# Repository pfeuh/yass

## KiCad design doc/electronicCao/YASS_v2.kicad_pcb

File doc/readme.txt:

Concerning Yass, all is shared.

Box data is explaned in yassBox.txt.
Schematic is in this folder.
To make the PCB, data is in fab folder.

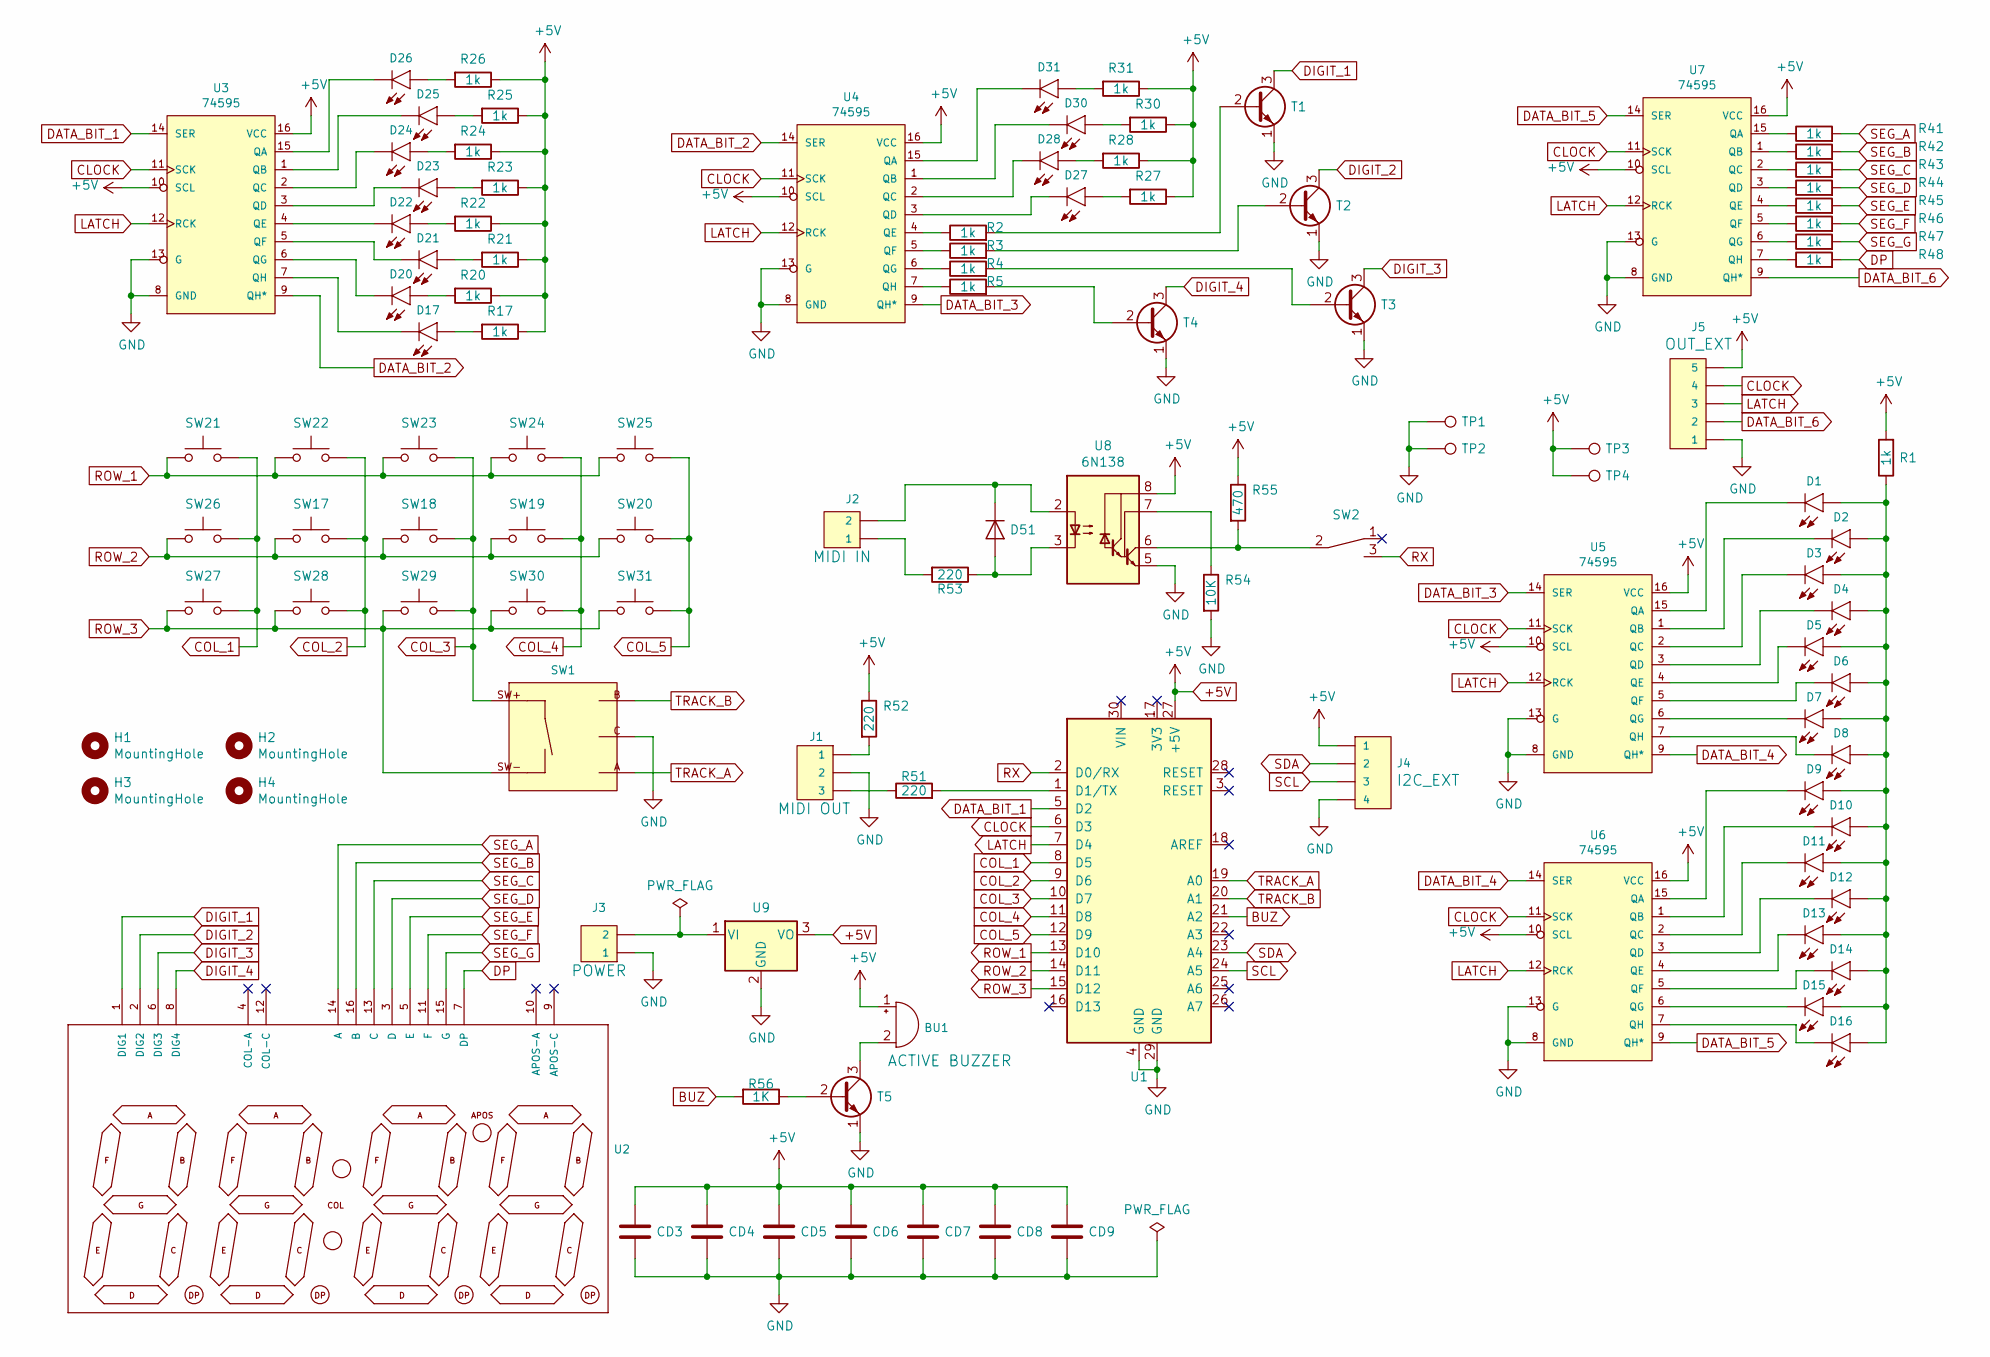
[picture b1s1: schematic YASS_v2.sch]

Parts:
BU1: BUZZER-PTH_KIT_NO_SILK; MagneticBuzzer_ProSignal_ABI-009-RC
CD3, CD4, CD5, CD6, CD7, CD8, CD9: 100nF; C_Disc_D4.3mm_W1.9mm_P5.00mm
D1, D2, D3, D4, D5, D6, D7, D8, D9, D10, D11, D12, D13, D14, D15, D16, D20: 3mm red; LED_3MM
D17: 3mm green; LED_3MM
D21, D22, D23, D24, D25: 3mm blue; LED_3MM
D26, D27, D28, D30, D31: 3mm yellow; LED_3MM
D51: 1N4148; DIODE
H1, H2, H3, H4: MountingHole; MountingHole_3.2mm_M3
J1: CONN_03; 1X03
J2: CONN_02; 1X02
J3: POWER CONNECTOR; 1X02
J4: CONN_04; 1X04
J5: CONN_05; 1X05
R1, R2, R3, R4, R5, R17, R20, R21, R22, R23, R24, R25, R26, R27, R28, R30, R31, R41, R42, R43, R44, R45, R46, R47, R48: 1k; R
R51, R52, R53: 220; R
R54: 10K; R
R55: 470; R
R56: 1K; R_Axial_DIN0207_L6.3mm_D2.5mm_P10.16mm_Horizontal
SW1: ENCODER-SWITCH; ROTARY_ENCODER
SW2: SWITCH_TOGGLE_SPST_RIGHT_ANGLE; SWITCH_SPDT_PTH_11.6X4.0MM
SW17, SW18, SW19, SW20, SW21, SW22, SW23, SW24, SW25, SW26, SW27, SW28, SW29, SW30, SW31: SW_Push; KEY_PUSH_6mm
T1, T3, T4, T5: 2N2222; TO-92_Inline_Narrow_Oval
T2: PN2222A; TO-92_Inline_Narrow_Oval
TP1, TP2, TP3, TP4: TestPoint; 1X01
U1: Arduino_Nano_v2.x; Arduino_Nano
U2: 7-SEGMENT-4DIGIT-10MM-RED; 4x7segments
U3, U4, U5, U6, U7: 74595; DIP16
U8: 6N138; DIP-8_W7.62mm
U9: LM7805_TO220; TO-220

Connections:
+5V: BU1.1 (-), CD3.1, CD4.1, CD5.1, CD6.1, CD7.1, CD8.1, CD9.1, J4.1, J5.5, R1.2, R17.1, R20.1, R21.1, R22.1, R23.1, R24.1, R25.1, R26.1, R27.1, R28.1, R30.1, R31.1, R52.1, R55.1, TP3.1, TP4.1, U1.27 (+5V), U3.10 (SCL), U3.16 (VCC), U4.10 (SCL), U4.16 (VCC), U5.10 (SCL), U5.16 (VCC), U6.10 (SCL), U6.16 (VCC), U7.10 (SCL), U7.16 (VCC), U8.8 (VCC), U9.3 (VO)
BUZ: R56.2, U1.21 (A2)
CLOCK: J5.4, U1.6 (D3), U3.11 (SCK), U4.11 (SCK), U5.11 (SCK), U6.11 (SCK), U7.11 (SCK)
COL_1: SW21.2, SW26.2, SW27.2, U1.8 (D5)
COL_2: SW17.2, SW22.2, SW28.2, U1.9 (D6)
COL_3: SW1.SW+, SW18.2, SW23.2, SW29.2, U1.10 (D7)
COL_4: SW19.2, SW24.2, SW30.2, U1.11 (D8)
COL_5: SW20.2, SW25.2, SW31.2, U1.12 (D9)
DATA_BIT_1: U1.5 (D2), U3.14 (SER)
DATA_BIT_2: U3.9 (QH*), U4.14 (SER)
DATA_BIT_3: U4.9 (QH*), U5.14 (SER)
DATA_BIT_4: U5.9 (QH*), U6.14 (SER)
DATA_BIT_5: U6.9 (QH*), U7.14 (SER)
DATA_BIT_6: J5.2, U7.9 (QH*)
DIGIT_1: T1.3 (C), U2.1 (DIG1)
DIGIT_2: T2.3 (C), U2.2 (DIG2)
DIGIT_3: T3.3 (C), U2.6 (DIG3)
DIGIT_4: T4.3 (C), U2.8 (DIG4)
DP: R48.2, U2.7 (DP)
GND: CD3.2, CD4.2, CD5.2, CD6.2, CD7.2, CD8.2, CD9.2, J1.2, J3.1, J4.4, J5.1, R54.2, SW1.C, T1.1 (E), T2.1 (E), T3.1 (E), T4.1 (E), T5.1 (E), TP1.1, TP2.1, U1.4 (GND), U1.29 (GND), U3.8 (GND), U3.13 (G), U4.8 (GND), U4.13 (G), U5.8 (GND), U5.13 (G), U6.8 (GND), U6.13 (G), U7.8 (GND), U7.13 (G), U8.5 (GND), U9.2 (GND)
LATCH: J5.3, U1.7 (D4), U3.12 (RCK), U4.12 (RCK), U5.12 (RCK), U6.12 (RCK), U7.12 (RCK)
unnamed: BU1.2 (+), T5.3 (C)
unnamed: D1.A, D2.A, D3.A, D4.A, D5.A, D6.A, D7.A, D8.A, D9.A, D10.A, D11.A, D12.A, D13.A, D14.A, D15.A, D16.A, R1.1
unnamed: D1.K (C), U5.15 (QA)
unnamed: D2.K (C), U5.1 (QB)
unnamed: D3.K (C), U5.2 (QC)
unnamed: D4.K (C), U5.3 (QD)
unnamed: D5.K (C), U5.4 (QE)
unnamed: D6.K (C), U5.5 (QF)
unnamed: D7.K (C), U5.6 (QG)
unnamed: D8.K (C), U5.7 (QH)
unnamed: D9.K (C), U6.15 (QA)
unnamed: D10.K (C), U6.1 (QB)
unnamed: D11.K (C), U6.2 (QC)
unnamed: D12.K (C), U6.3 (QD)
unnamed: D13.K (C), U6.4 (QE)
unnamed: D14.K (C), U6.5 (QF)
unnamed: D15.K (C), U6.6 (QG)
unnamed: D16.K (C), U6.7 (QH)
unnamed: D17.A, R17.2
unnamed: D17.K (C), U3.7 (QH)
unnamed: D20.A, R20.2
unnamed: D20.K (C), U3.6 (QG)
unnamed: D21.A, R21.2
unnamed: D21.K (C), U3.5 (QF)
unnamed: D22.A, R22.2
unnamed: D22.K (C), U3.4 (QE)
unnamed: D23.A, R23.2
unnamed: D23.K (C), U3.3 (QD)
unnamed: D24.A, R24.2
unnamed: D24.K (C), U3.2 (QC)
unnamed: D25.A, R25.2
unnamed: D25.K (C), U3.1 (QB)
unnamed: D26.A, R26.2
unnamed: D26.K (C), U3.15 (QA)
unnamed: D27.A, R27.2
unnamed: D27.K (C), U4.3 (QD)
unnamed: D28.A, R28.2
unnamed: D28.K (C), U4.2 (QC)
unnamed: D30.A, R30.2
unnamed: D30.K (C), U4.1 (QB)
unnamed: D31.A, R31.2
unnamed: D31.K (C), U4.15 (QA)
unnamed: D51.1 (K), J2.2, U8.2 (C1)
unnamed: D51.2 (A), R53.1, U8.3 (C2)
unnamed: J1.1, R52.2
unnamed: J1.3, R51.1
unnamed: J2.1, R53.2
unnamed: J3.2, U9.1 (VI)
unnamed: R2.1, U4.4 (QE)
unnamed: R2.2, T1.2 (B)
unnamed: R3.1, U4.5 (QF)
unnamed: R3.2, T2.2 (B)
unnamed: R4.1, U4.6 (QG)
unnamed: R4.2, T3.2 (B)
unnamed: R5.1, U4.7 (QH)
unnamed: R5.2, T4.2 (B)
unnamed: R41.1, U7.15 (QA)
unnamed: R42.1, U7.1 (QB)
unnamed: R43.1, U7.2 (QC)
unnamed: R44.1, U7.3 (QD)
unnamed: R45.1, U7.4 (QE)
unnamed: R46.1, U7.5 (QF)
unnamed: R47.1, U7.6 (QG)
unnamed: R48.1, U7.7 (QH)
unnamed: R51.2, U1.1 (D1/TX)
unnamed: R54.1, U8.7 (VO1)
unnamed: R55.2, SW2.2, U8.6 (VO2)
unnamed: R56.1, T5.2 (B)
ROW_1: SW21.1, SW22.1, SW23.1, SW24.1, SW25.1, U1.13 (D10)
ROW_2: SW17.1, SW18.1, SW19.1, SW20.1, SW26.1, U1.14 (D11)
ROW_3: SW1.SW-, SW27.1, SW28.1, SW29.1, SW30.1, SW31.1, U1.15 (D12)
RX: SW2.3, U1.2 (D0/RX)
SCL: J4.3, U1.24 (A5)
SDA: J4.2, U1.23 (A4)
SEG_A: R41.2, U2.14 (A)
SEG_B: R42.2, U2.16 (B)
SEG_C: R43.2, U2.13 (C)
SEG_D: R44.2, U2.3 (D)
SEG_E: R45.2, U2.5 (E)
SEG_F: R46.2, U2.11 (F)
SEG_G: R47.2, U2.15 (G)
TRACK_A: SW1.A, U1.19 (A0)
TRACK_B: SW1.B, U1.20 (A1)

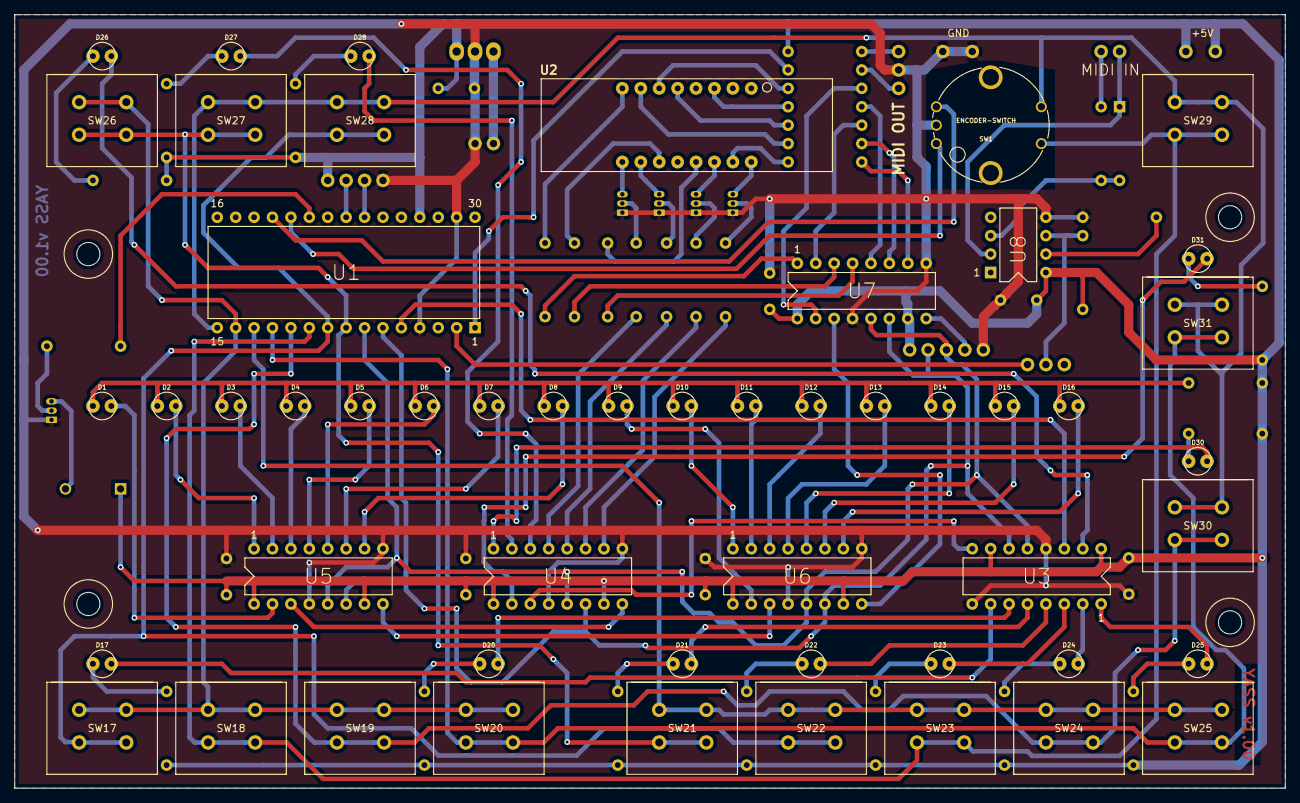
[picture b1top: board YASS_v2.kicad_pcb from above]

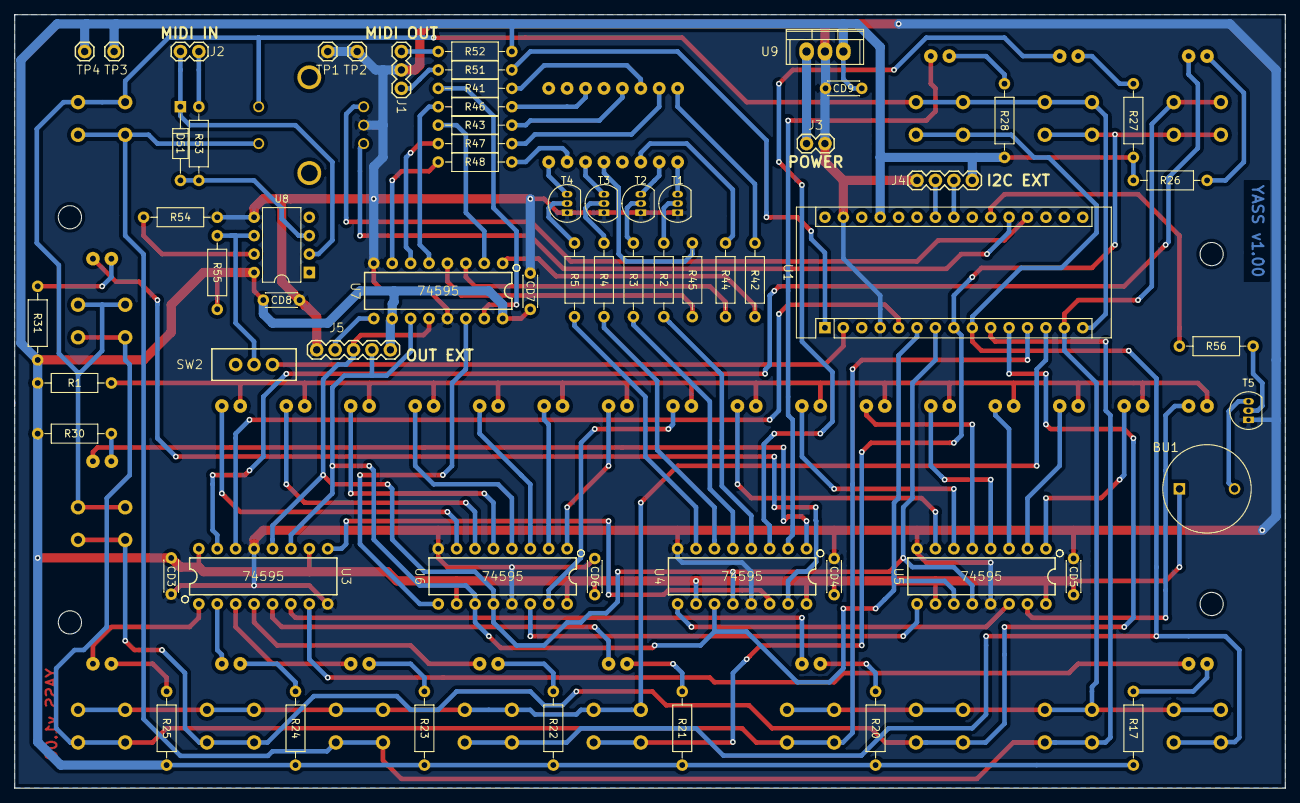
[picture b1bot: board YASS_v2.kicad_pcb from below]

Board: 2 copper layers, 175.3 x 106.7 mm, 112 parts (63 on the bottom side), 104 nets.

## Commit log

2019-08-29 adds some documentation files
2019-08-29 Adds code for midi clock in Adds a bpm computation when using external clock
2019-08-29 Better precision for BPM computation
2019-08-30 Adds sequence dump sending
2019-08-30 reception of sequences dump working
2019-08-31 Add part of sending/receiving global dump bug not fixed an another bug in displaying splash screen 'fact'
2019-08-31 Adds specific folders in doc dedicated to yass front pannel
2019-08-31 bug fixed: lower/upper case problem in filename yassSysEx
2019-08-31 has not bo be in repository
2019-08-31 front pannel serigraphie drawn. first version
2019-09-01 front pannel black text on white board v.5
2019-09-01 Adds file for laser cut machine
2019-09-01 global config default setup done.
2019-09-01 dump requests implemented
2019-09-03 Adds a maintenance mode and responds to remoted dump
2019-09-03 Adds a 200msec debouncing
2019-09-03 unused file
2019-09-03 last commit before changing start stop continue behavior
2019-09-04 key Continue replaced by ket Previous. Start Stop Continue assumed now by keys Start Stop
2019-09-04 adds a base for free eeprom bytes
2019-09-04 adds a test to write eeprom and an bad midi bytes checker
2019-09-04 attempt to create a decent serigraphy
2019-09-05 adds somr 3D objects
2019-09-05 electronic board added
2019-09-05 adds 3D objects
2019-09-05 another attempt to make a decent file for laser cut machine
2019-09-07 creration of decent bill of material
2019-09-07 adds a readme to describe biefly the YASS
2019-09-08 modifications on 3D gears
2019-09-09 new python script to generate files for lasercut machine
2019-09-10 adds code to generate a csv file with coordinates of objects
2019-09-10 coquilles dans le texte
2019-09-11 yassConfFsm renamed yassEditFsm - file yassDevelopmentBook created
2019-09-11 ajout du yassDevelopmentBook. Reéorganisation totale de l'utilisation de yassEditFsm. Renaming de plusieurs #define.
2019-09-12 adds some texr in doc.
2019-09-12 littles changes in yassDisplay, numbers are now right justified
2019-09-13 working on manuals - working on bottons on/off logic
2019-09-17 yassMonostable v1.01 - add a isBusy() method
2019-09-17 yass Sequencer 2019 09 17 - v1.01 - recording only until last step
2019-09-17 Adds some text to user manual
2019-09-18 some work on buttons logic & record mode
2019-09-18 ajout panneau arriere teko avec les connecteurs
2019-09-28 adds a pattern to drillyassBackPannelTeko
2019-10-05 Adds face avant boite centrakor
2019-10-06 Correction of centrakord board holes coordinates
2019-10-09 proto console added
2019-10-09 add encoder on consoleproto
